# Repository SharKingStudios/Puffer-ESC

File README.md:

# Puffer ESC — A Ridiculous Little Combat Robot ESC

### Named for what it will do to your battery.

Puffer is a compact, three-phase brushless ESC designed to push the limits of current handling in combat robotics.

Rather than using a single MOSFET per switching position, Puffer uses three in parallel, bringing the total to **18 MOSFETs on a 75 × 30 mm PCB**. The goal is to reduce conduction losses and improve current handling without significantly increasing the footprint of the ESC.

Of course, throwing more MOSFETs at the problem doesn't magically make this a 300A ESC. Actual performance will depend on PCB resistance, current sharing, switching losses, and thermal management.

But 18 MOSFETs on a tiny PCB looks ridiculous, and that's reason enough to try it.

> **Where this project is at:** Hardware designed; assembly, firmware development, and performance tests are pending.

## Renders

Because everyone loves eye candy.

## Hardware Specifications

| Specification | Details |
| :--- | :--- |
| Motor Type | Three-phase brushless DC (BLDC) |
| PCB Dimensions | 75 × 30 mm |
| PCB Stackup | 4 layers |
| Microcontroller | AT32F421G8U7 |
| Gate Driver | DRV8320HRTVR |
| MOSFETs | 18 × HYG025N06LS1C2 (60 V) |
| Power Stage | Six switching banks, three MOSFETs per bank |
| Current Sense Amplifier | INA186A2IDCKR |
| Current Shunt | ASR-M-5-0.2F (0.2 mΩ) |
| Temperature Sensor | 10 kΩ NTC thermistor |
| Buck Converter | LMR16006XDDCR |
| Power Distribution | Double-sided copper bus bars |
| DC-Link Filtering | Onboard capacitors |
| Cooling | Aluminum heatsink covering all 18 MOSFETs |
| Continuous Current Rating | TBD — pending testing |
| Peak Current Rating | TBD — pending testing |

The complete bill of materials is available in [BOM.csv](./BOM.csv).

## Next Steps

- Assemble the first boards.
- Develop and tune the motor-control firmware.
- Stress test the power stage.
- Measure maximum sustained and peak current capability.
- Put it in a combat robot and see what happens?

---

## Contributing

Ideas, improvements, design reviews, and constructive roasting are welcome.

Feel free to open an issue or submit a pull request. Feedback on the hardware, firmware, and overall design is appreciated, especially if you've spotted something I've overlooked.

## Disclaimer

Puffer is an experimental, open-source hardware project, not a commercially validated ESC. Its performance, reliability, and operating limits have yet to be established.

Working with high currents, spinning motors, and stored electrical energy carries inherent risks. Exercise appropriate safety precautions when assembling, powering, or testing this hardware.

If you short something or accidentally turn your robot into a very expensive space heater, that's on you.

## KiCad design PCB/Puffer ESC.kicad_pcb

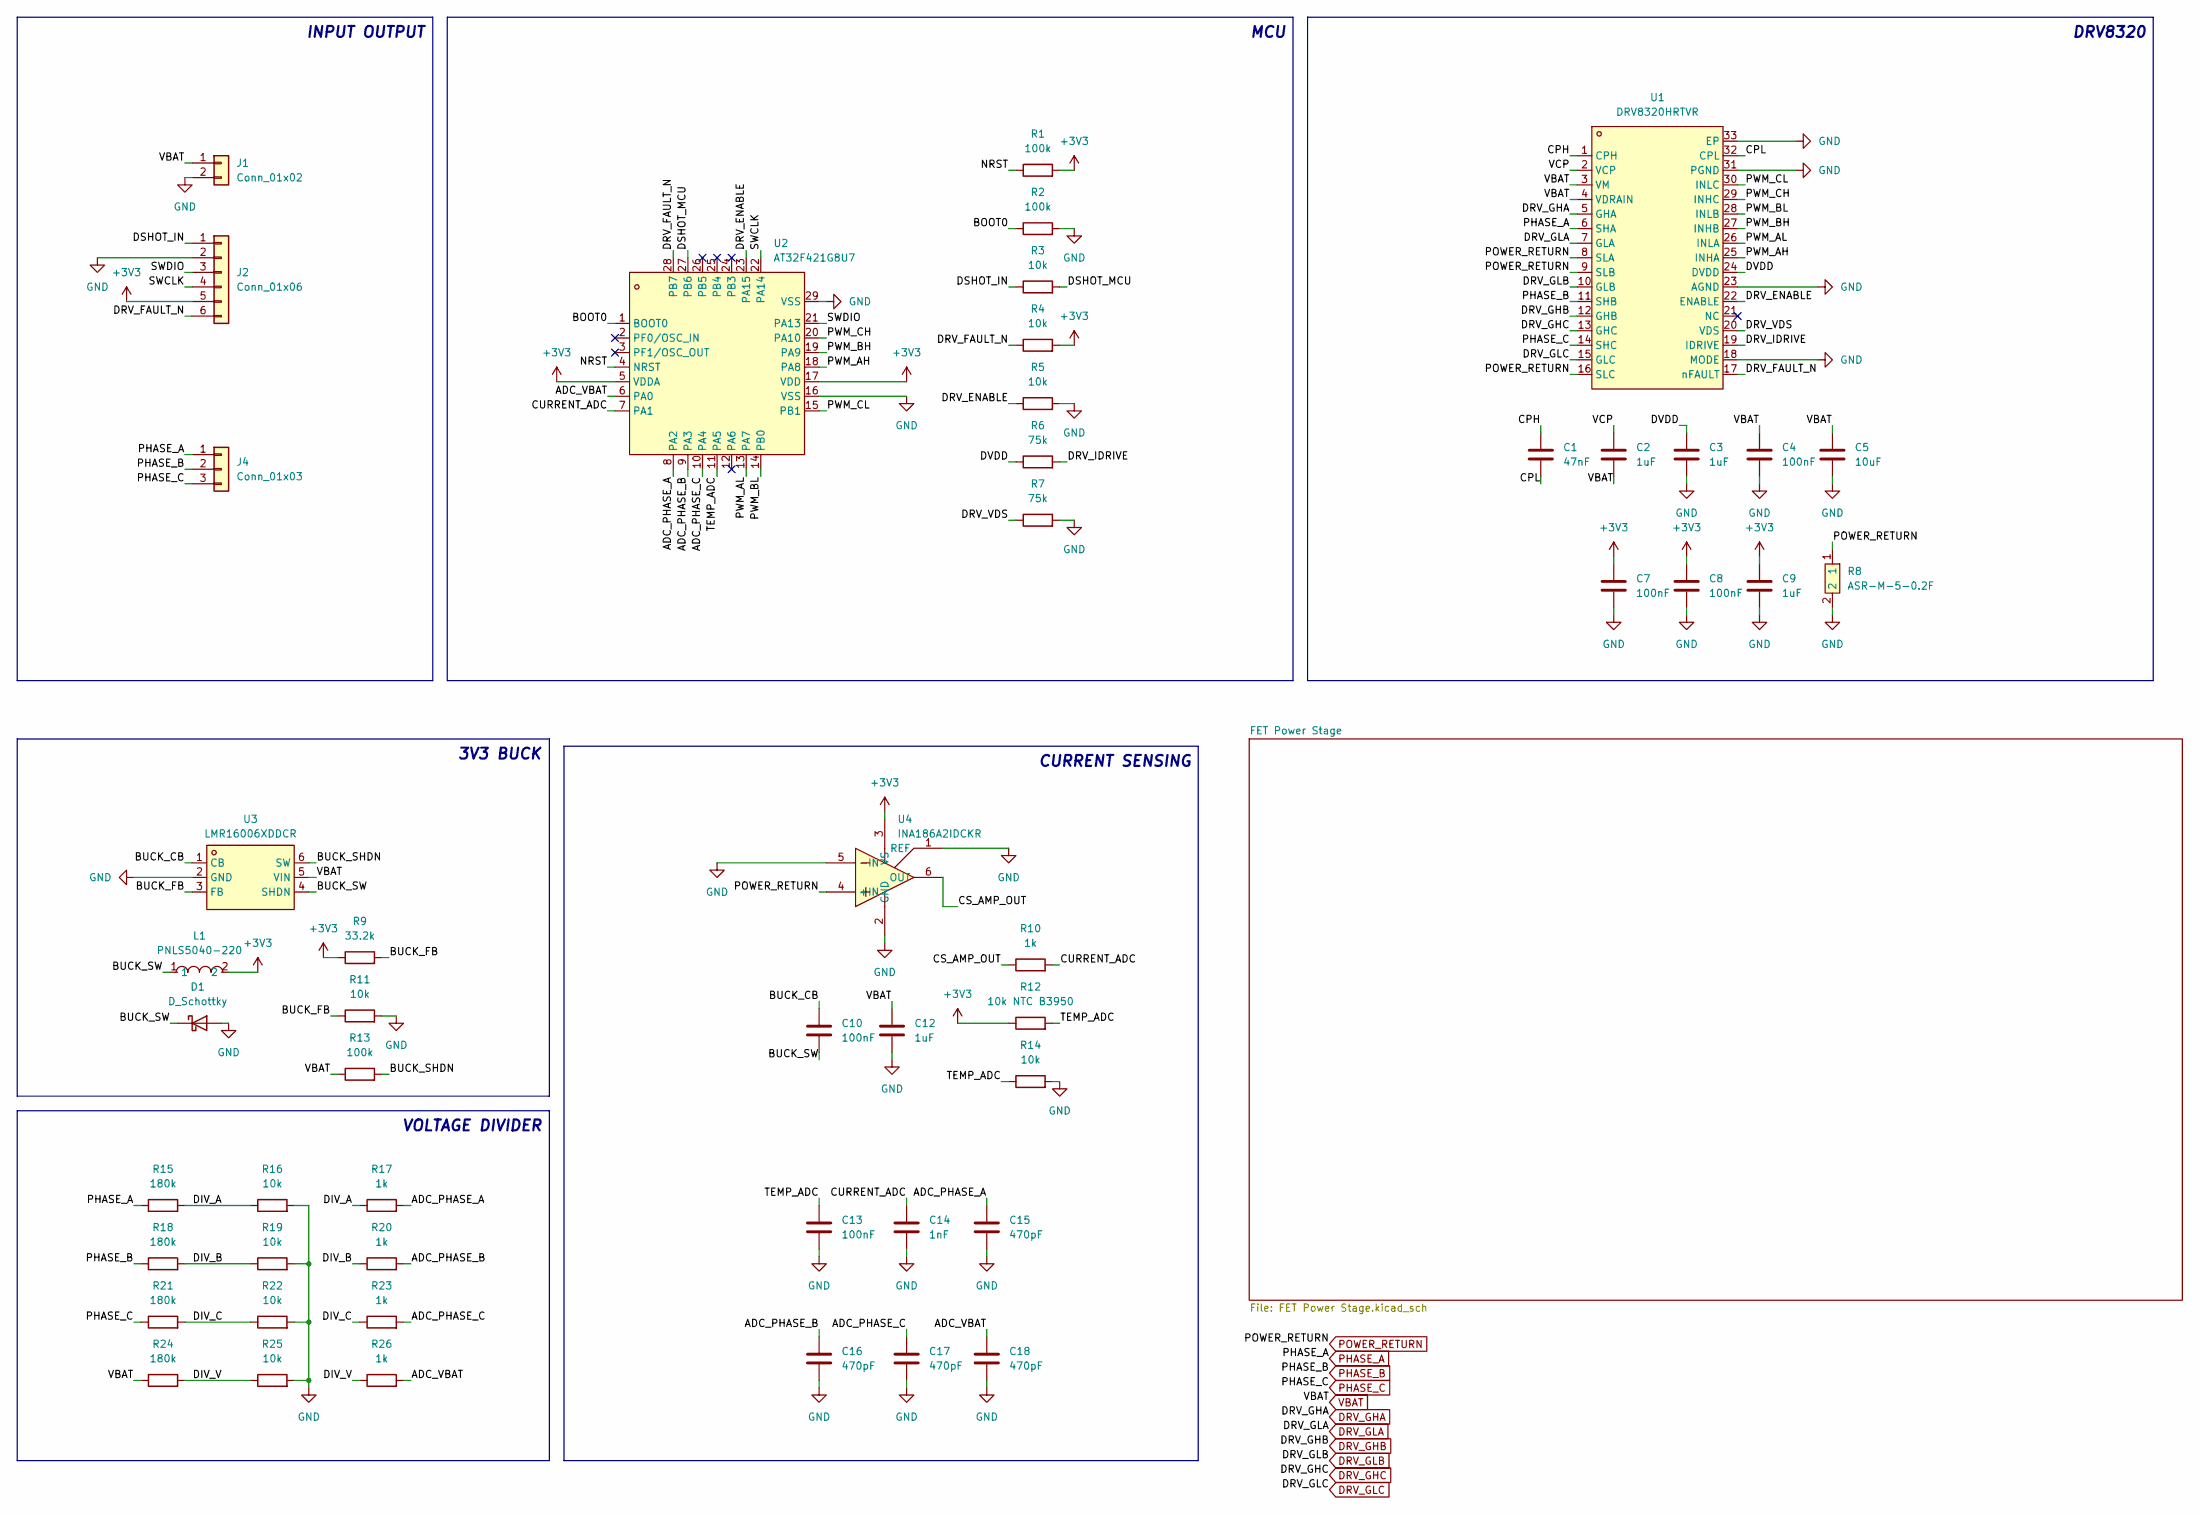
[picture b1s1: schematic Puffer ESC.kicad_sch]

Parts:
C1: 47nF; C_0603_1608Metric
C2, C12: 1uF; C_0805_2012Metric
C3, C9: 1uF; C_0603_1608Metric
C4, C7, C8, C10, C13: 100nF; C_0603_1608Metric
C5: 10uF; C_1210_3225Metric
C14: 1nF; C_0603_1608Metric
C15, C16, C17, C18: 470pF; C_0603_1608Metric
D1: D_Schottky; D_SMA
J1: Conn_01x02; AMASS_XT30UPB-F_1x02_P5.0mm_Vertical
J2: Conn_01x06; PinHeader_1x06_P2.54mm_Vertical_SMD_Pin1Left
J4: Conn_01x03; SolderWire-2.5sqmm_1x03_P7.2mm_D2.4mm_OD3.6mm
L1: PNLS5040-220; IND-SMD_L5.0-W5.0; MPN PNLS5040-220M 22UH; LCSC Part C2849503
R1, R2, R13: 100k; R_0603_1608Metric
R3, R4, R5, R11, R14, R16, R19, R22, R25: 10k; R_0603_1608Metric
R6, R7: 75k; R_0603_1608Metric
R8: ASR-M-5-0.2F; R3920; MPN ASR-M-5-0.2F; LCSC Part C6075495
R9: 33.2k; R_0603_1608Metric
R10, R17, R20, R23, R26: 1k; R_0603_1608Metric
R12: 10k NTC B3950; R_0603_1608Metric
R15, R18, R21, R24: 180k; R_0603_1608Metric
U1: DRV8320HRTVR; QFN-32_L5.0-W5.0-P0.50-TL-EP3.5; MPN DRV8320HRTVR; LCSC Part C701782
U2: AT32F421G8U7; QFN-28_L4.0-W4.0-P0.40-TL-EP2.4; MPN AT32F421G8U7; LCSC Part C2765098
U3: LMR16006XDDCR; SOT-23-6_L2.9-W1.6-P0.95-LS2.8-BR; MPN LMR16006XDDCR; LCSC Part C87080
U4: INA186A2IDCKR; SC-70-6_L2.0-W1.3-P0.65-LS2.1-BL-1; MPN INA186A3IDCKR; LCSC Part C2058245

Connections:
+3V3: C7.1, C8.1, C9.1, J2.5, L1.2, R1.2, R4.2, R9.1, R12.1, U2.5 (VDDA), U2.17 (VDD), U4.3 (VS); also elsewhere on the board
/ADC_PHASE_A: C15.1, R17.2, U2.8 (PA2)
/ADC_PHASE_B: C16.1, R20.2, U2.9 (PA3)
/ADC_PHASE_C: C17.1, R23.2, U2.10 (PA4)
/ADC_VBAT: C18.1, R26.2, U2.6 (PA0)
/BOOT0: R2.1, U2.1 (BOOT0)
/BUCK_CB: C10.1, U3.1 (CB)
/BUCK_FB: R9.2, R11.1, U3.3 (FB)
/BUCK_SHDN: R13.2, U3.6 (SW)
/BUCK_SW: C10.2, D1.1 (K), L1.1, U3.4 (SHDN)
/CPH: C1.1, U1.1 (CPH)
/CPL: C1.2, U1.32 (CPL)
/CS_AMP_OUT: R10.1, U4.6 (OUT)
/CURRENT_ADC: C14.1, R10.2, U2.7 (PA1)
/DIV_A: R15.2, R16.1, R17.1
/DIV_B: R18.2, R19.1, R20.1
/DIV_C: R21.2, R22.1, R23.1
/DIV_V: R24.2, R25.1, R26.1
/DRV_ENABLE: R5.1, U1.22 (ENABLE), U2.23 (PA15)
/DRV_FAULT_N: J2.6, R4.1, U1.17 (nFAULT), U2.28 (PB7)
/DRV_IDRIVE: R6.2, U1.19 (IDRIVE)
/DRV_VDS: R7.1, U1.20 (VDS)
/DSHOT_IN: J2.1, R3.1
/DSHOT_MCU: R3.2, U2.27 (PB6)
/DVDD: C3.1, R6.1, U1.24 (DVDD)
/NRST: R1.1, U2.4 (NRST)
/PWM_AH: U1.25 (INHA), U2.18 (PA8)
/PWM_AL: U1.26 (INLA), U2.13 (PA7)
/PWM_BH: U1.27 (INHB), U2.19 (PA9)
/PWM_BL: U1.28 (INLB), U2.14 (PB0)
/PWM_CH: U1.29 (INHC), U2.20 (PA10)
/PWM_CL: U1.30 (INLC), U2.15 (PB1)
/SWCLK: J2.4, U2.22 (PA14)
/SWDIO: J2.3, U2.21 (PA13)
/TEMP_ADC: C13.1, R12.2, R14.1, U2.11 (PA5)
/VCP: C2.1, U1.2 (VCP)
DRV_GHA: U1.5 (GHA); also elsewhere on the board
DRV_GHB: U1.12 (GHB); also elsewhere on the board
DRV_GHC: U1.13 (GHC); also elsewhere on the board
DRV_GLA: U1.7 (GLA); also elsewhere on the board
DRV_GLB: U1.10 (GLB); also elsewhere on the board
DRV_GLC: U1.15 (GLC); also elsewhere on the board
GND: C3.2, C4.2, C5.2, C7.2, C8.2, C9.2, C12.2, C13.2, C14.2, C15.2, C16.2, C17.2, C18.2, D1.2 (A), J1.2, J2.2, R2.2, R5.2, R7.2, R8.2, R11.2, R14.2, R16.2, R19.2, R22.2, R25.2, U1.18 (MODE), U1.23 (AGND), U1.31 (PGND), U1.33 (EP), U2.16 (VSS), U2.29 (VSS), U3.2 (GND), U4.1 (REF), U4.2 (GND), U4.5 (-IN); also elsewhere on the board
PHASE_A: J4.1, R15.1, U1.6 (SHA); also elsewhere on the board
PHASE_B: J4.2, R18.1, U1.11 (SHB); also elsewhere on the board
PHASE_C: J4.3, R21.1, U1.14 (SHC); also elsewhere on the board
POWER_RETURN: R8.1, U1.8 (SLA), U1.9 (SLB), U1.16 (SLC), U4.4 (+IN); also elsewhere on the board
VBAT: C2.2, C4.1, C5.1, C12.1, J1.1, R13.1, R24.1, U1.3 (VM), U1.4 (VDRAIN), U3.5 (VIN); also elsewhere on the board

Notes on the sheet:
CURRENT SENSING
VOLTAGE DIVIDER
INPUT OUTPUT
MCU
DRV8320
3V3 BUCK

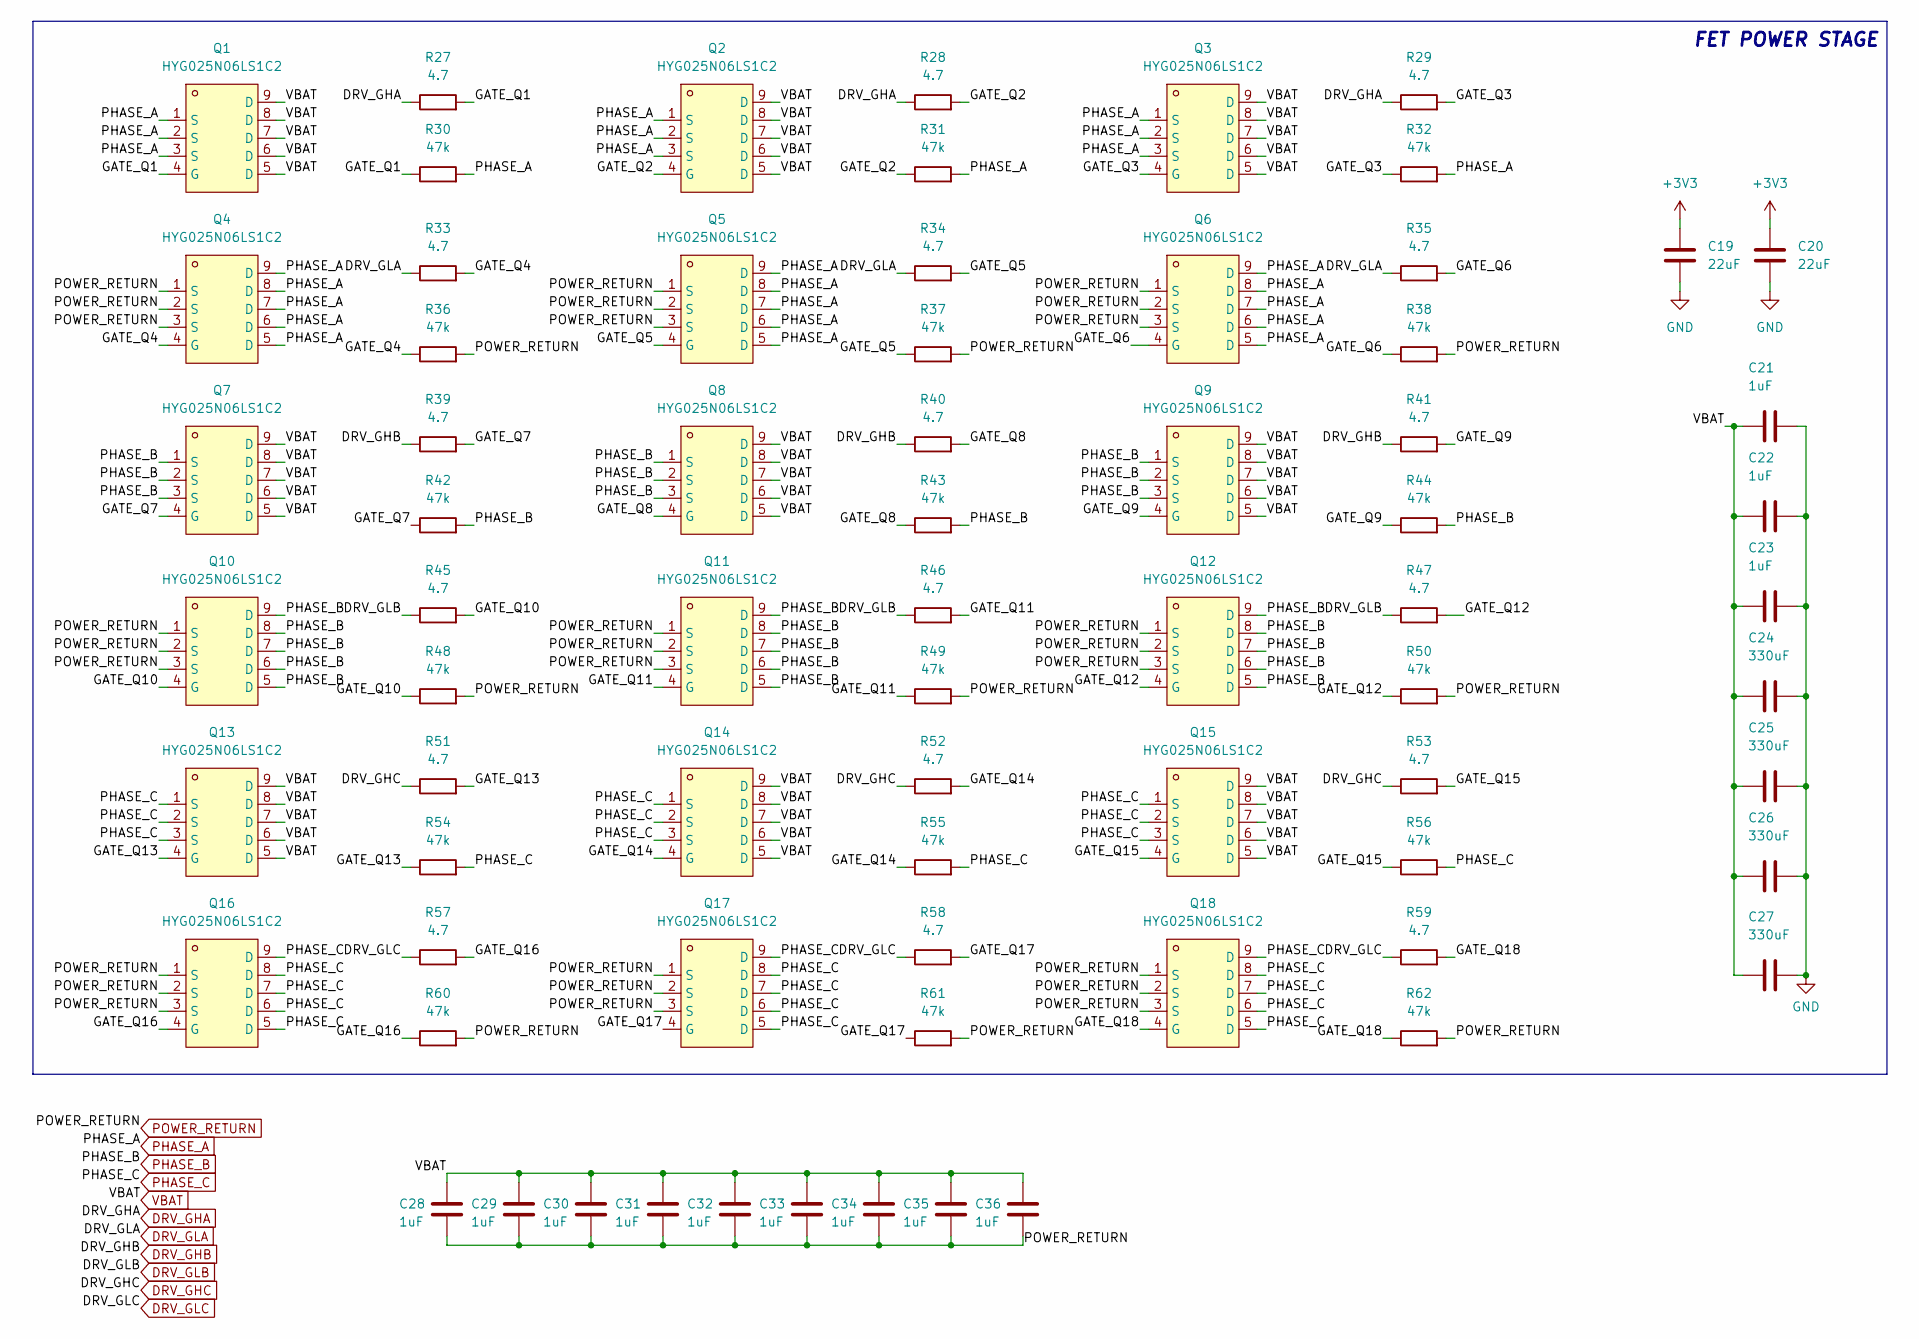
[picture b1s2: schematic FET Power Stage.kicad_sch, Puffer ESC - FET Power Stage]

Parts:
C19, C20: 22uF; C_1206_3216Metric
C21, C22, C23, C28, C29, C30, C31, C32, C33, C34, C35, C36: 1uF; C_0805_2012Metric
C24, C25, C26, C27: 330uF; C_1206_3216Metric
Q1, Q2, Q3, Q4, Q5, Q6, Q7, Q8, Q9, Q10, Q11, Q12, Q13, Q14, Q15, Q16, Q17, Q18: HYG025N06LS1C2; DFN-8_L5.9-W5.2-P1.27-LS6.2-BL; MPN HYG025N06LS1C2; LCSC Part C2827231
R27, R28, R29, R33, R34, R35, R39, R40, R41, R45, R46, R47, R51, R52, R53, R57, R58, R59: 4.7; R_0603_1608Metric
R30, R31, R32, R36, R37, R38, R42, R43, R44, R48, R49, R50, R54, R55, R56, R60, R61, R62: 47k; R_0603_1608Metric

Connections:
+3V3: C19.1, C20.1; also elsewhere on the board
/FET Power Stage/GATE_Q1: Q1.4 (G), R27.2, R30.1
/FET Power Stage/GATE_Q2: Q2.4 (G), R28.2, R31.1
/FET Power Stage/GATE_Q3: Q3.4 (G), R29.2, R32.1
/FET Power Stage/GATE_Q4: Q4.4 (G), R33.2, R36.1
/FET Power Stage/GATE_Q5: Q5.4 (G), R34.2, R37.1
/FET Power Stage/GATE_Q6: Q6.4 (G), R35.2, R38.1
/FET Power Stage/GATE_Q7: Q7.4 (G), R39.2, R42.1
/FET Power Stage/GATE_Q8: Q8.4 (G), R40.2, R43.1
/FET Power Stage/GATE_Q9: Q9.4 (G), R41.2, R44.1
/FET Power Stage/GATE_Q10: Q10.4 (G), R45.2, R48.1
/FET Power Stage/GATE_Q11: Q11.4 (G), R46.2, R49.1
/FET Power Stage/GATE_Q12: Q12.4 (G), R47.2, R50.1
/FET Power Stage/GATE_Q13: Q13.4 (G), R51.2, R54.1
/FET Power Stage/GATE_Q14: Q14.4 (G), R52.2, R55.1
/FET Power Stage/GATE_Q15: Q15.4 (G), R53.2, R56.1
/FET Power Stage/GATE_Q16: Q16.4 (G), R57.2, R60.1
/FET Power Stage/GATE_Q17: Q17.4 (G), R58.2, R61.1
/FET Power Stage/GATE_Q18: Q18.4 (G), R59.2, R62.1
DRV_GHA: R27.1, R28.1, R29.1; also elsewhere on the board
DRV_GHB: R39.1, R40.1, R41.1; also elsewhere on the board
DRV_GHC: R51.1, R52.1, R53.1; also elsewhere on the board
DRV_GLA: R33.1, R34.1, R35.1; also elsewhere on the board
DRV_GLB: R45.1, R46.1, R47.1; also elsewhere on the board
DRV_GLC: R57.1, R58.1, R59.1; also elsewhere on the board
GND: C19.2, C20.2, C21.2, C22.2, C23.2, C24.2, C25.2, C26.2, C27.2; also elsewhere on the board
PHASE_A: Q1.1 (S), Q1.2 (S), Q1.3 (S), Q2.1 (S), Q2.2 (S), Q2.3 (S), Q3.1 (S), Q3.2 (S), Q3.3 (S), Q4.5 (D), Q4.6 (D), Q4.7 (D), Q4.8 (D), Q4.9 (D), Q5.5 (D), Q5.6 (D), Q5.7 (D), Q5.8 (D), Q5.9 (D), Q6.5 (D), Q6.6 (D), Q6.7 (D), Q6.8 (D), Q6.9 (D), R30.2, R31.2, R32.2; also elsewhere on the board
PHASE_B: Q7.1 (S), Q7.2 (S), Q7.3 (S), Q8.1 (S), Q8.2 (S), Q8.3 (S), Q9.1 (S), Q9.2 (S), Q9.3 (S), Q10.5 (D), Q10.6 (D), Q10.7 (D), Q10.8 (D), Q10.9 (D), Q11.5 (D), Q11.6 (D), Q11.7 (D), Q11.8 (D), Q11.9 (D), Q12.5 (D), Q12.6 (D), Q12.7 (D), Q12.8 (D), Q12.9 (D), R42.2, R43.2, R44.2; also elsewhere on the board
PHASE_C: Q13.1 (S), Q13.2 (S), Q13.3 (S), Q14.1 (S), Q14.2 (S), Q14.3 (S), Q15.1 (S), Q15.2 (S), Q15.3 (S), Q16.5 (D), Q16.6 (D), Q16.7 (D), Q16.8 (D), Q16.9 (D), Q17.5 (D), Q17.6 (D), Q17.7 (D), Q17.8 (D), Q17.9 (D), Q18.5 (D), Q18.6 (D), Q18.7 (D), Q18.8 (D), Q18.9 (D), R54.2, R55.2, R56.2; also elsewhere on the board
POWER_RETURN: C28.1, C29.1, C30.1, C31.1, C32.1, C33.1, C34.1, C35.1, C36.1, Q4.1 (S), Q4.2 (S), Q4.3 (S), Q5.1 (S), Q5.2 (S), Q5.3 (S), Q6.1 (S), Q6.2 (S), Q6.3 (S), Q10.1 (S), Q10.2 (S), Q10.3 (S), Q11.1 (S), Q11.2 (S), Q11.3 (S), Q12.1 (S), Q12.2 (S), Q12.3 (S), Q16.1 (S), Q16.2 (S), Q16.3 (S), Q17.1 (S), Q17.2 (S), Q17.3 (S), Q18.1 (S), Q18.2 (S), Q18.3 (S), R36.2, R37.2, R38.2, R48.2, R49.2, R50.2, R60.2, R61.2, R62.2; also elsewhere on the board
VBAT: C21.1, C22.1, C23.1, C24.1, C25.1, C26.1, C27.1, C28.2, C29.2, C30.2, C31.2, C32.2, C33.2, C34.2, C35.2, C36.2, Q1.5 (D), Q1.6 (D), Q1.7 (D), Q1.8 (D), Q1.9 (D), Q2.5 (D), Q2.6 (D), Q2.7 (D), Q2.8 (D), Q2.9 (D), Q3.5 (D), Q3.6 (D), Q3.7 (D), Q3.8 (D), Q3.9 (D), Q7.5 (D), Q7.6 (D), Q7.7 (D), Q7.8 (D), Q7.9 (D), Q8.5 (D), Q8.6 (D), Q8.7 (D), Q8.8 (D), Q8.9 (D), Q9.5 (D), Q9.6 (D), Q9.7 (D), Q9.8 (D), Q9.9 (D), Q13.5 (D), Q13.6 (D), Q13.7 (D), Q13.8 (D), Q13.9 (D), Q14.5 (D), Q14.6 (D), Q14.7 (D), Q14.8 (D), Q14.9 (D), Q15.5 (D), Q15.6 (D), Q15.7 (D), Q15.8 (D), Q15.9 (D); also elsewhere on the board

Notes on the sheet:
FET POWER STAGE

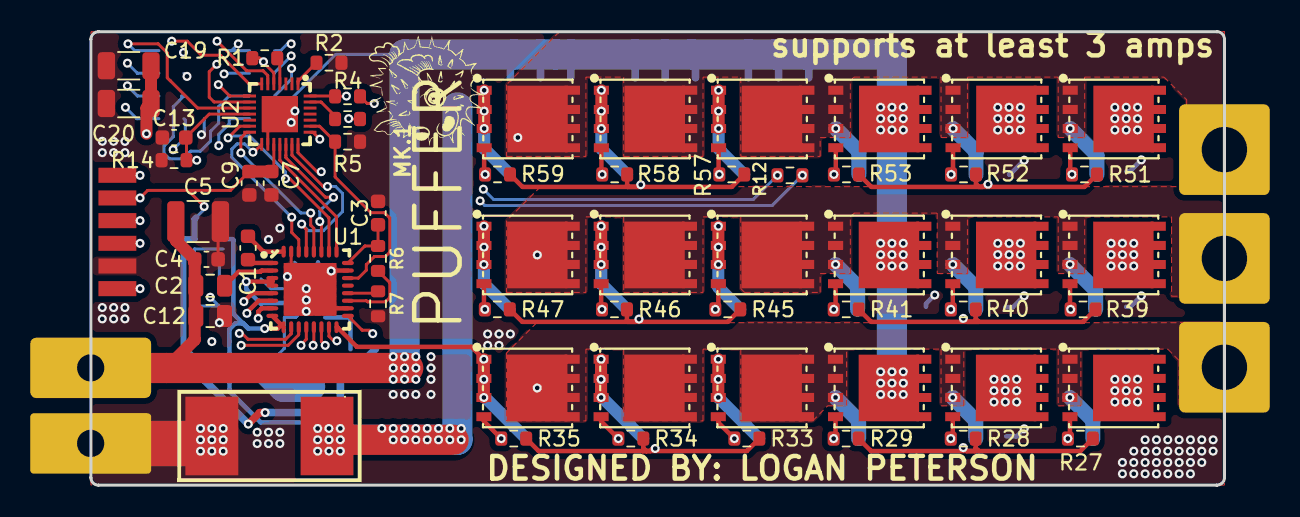
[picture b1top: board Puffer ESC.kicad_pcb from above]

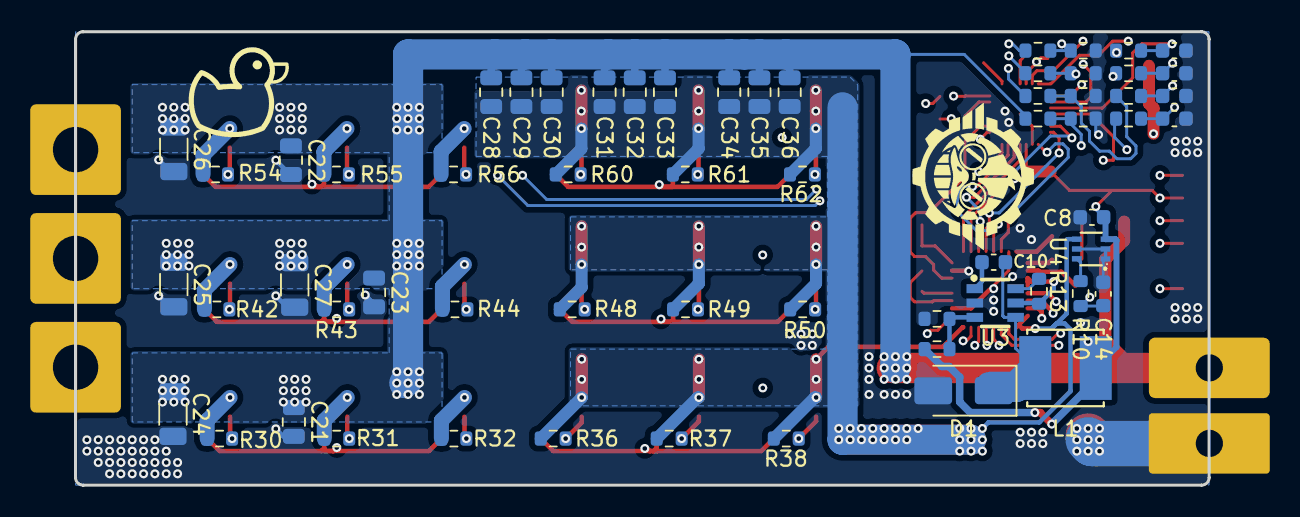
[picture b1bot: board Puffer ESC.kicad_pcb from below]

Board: 4 copper layers, 75.0 x 30.0 mm, 123 parts (61 on the bottom side), 66 nets.
